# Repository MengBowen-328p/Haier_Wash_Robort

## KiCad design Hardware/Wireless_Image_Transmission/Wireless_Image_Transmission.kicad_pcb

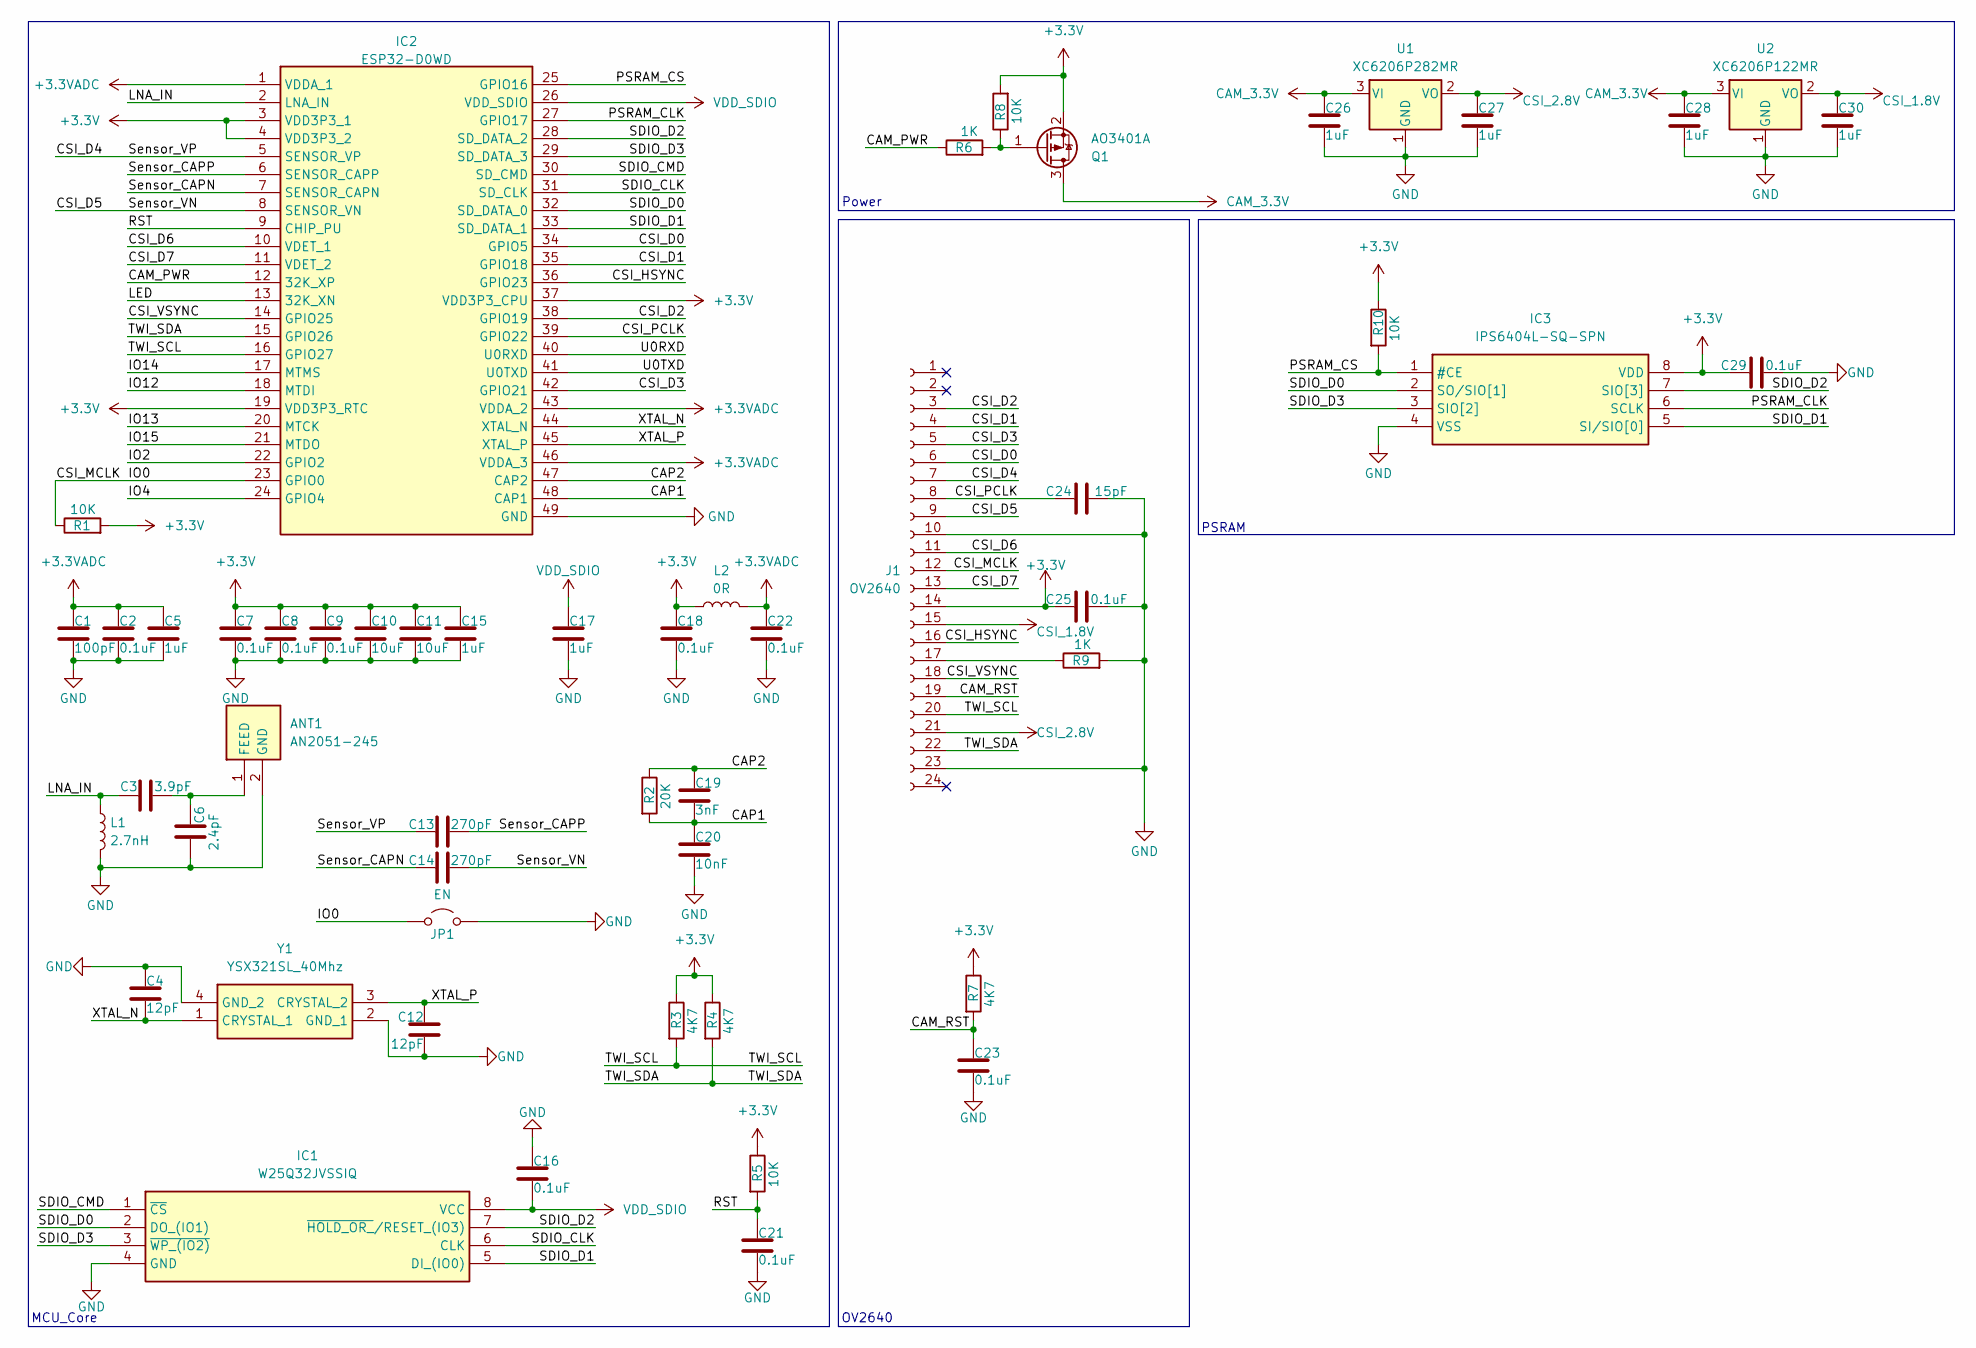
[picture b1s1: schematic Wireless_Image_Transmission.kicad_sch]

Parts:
ANT1: AN2051-245; ANTC5020X127N; Manufacturer_Part_Number AN2051-245
C1: 100pF; C_0402_1005Metric
C2, C7, C8, C9, C16, C18, C21, C22, C23, C25, C29: 0.1uF; C_0402_1005Metric
C3: 3.9pF; C_0402_1005Metric
C4, C12: 12pF; C_0402_1005Metric
C5, C15, C17: 1uF; C_0402_1005Metric
C6: 2.4pF; C_0402_1005Metric
C10, C11: 10uF; C_0402_1005Metric
C13, C14: 270pF; C_0402_1005Metric
C19: 3nF; C_0402_1005Metric
C20: 10nF; C_0402_1005Metric
C24: 15pF; C_0402_1005Metric
C26, C27, C28, C30: 1uF; C_0603_1608Metric
IC1: W25Q32JVSSIQ; SOIC127P790X216-8N; Manufacturer_Part_Number W25Q32JVSSIQ; Mouser Part Number 454-W25Q32JVSSIQ
IC2: ESP32-D0WD; QFN40P600X600X90-49N-D; Manufacturer_Part_Number ESP32-D0WD; Mouser Part Number 356-ESP32-D0WD
IC3: IPS6404L-SQ-SPN; SOIC127P600X175-8N; Manufacturer_Part_Number IPS6404L-SQ-SPN
J1: OV2640; TE_2-1734839-4_1x24-1MP_P0.5mm_Horizontal
JP1: EN; SolderJumper-2_P1.3mm_Open_RoundedPad1.0x1.5mm
L1: 2.7nH; L_0402_1005Metric_Pad0.77x0.64mm_HandSolder
L2: 0R; L_0402_1005Metric_Pad0.77x0.64mm_HandSolder
Q1: AO3401A; SOT-23
R1, R5, R8, R10: 10K; R_0402_1005Metric
R2: 20K; R_0402_1005Metric
R3, R4, R7: 4K7; R_0402_1005Metric
R6, R9: 1K; R_0402_1005Metric
U1: XC6206P282MR; SOT-23-3
U2: XC6206P122MR; SOT-23-3
Y1: YSX321SL_40Mhz; YSX321SL; Manufacturer_Part_Number YSX321SL

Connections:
+3.3V: C7.1, C8.1, C9.1, C10.1, C11.1, C15.1, C18.1, C25.1, C29.1, IC2.3 (VDD3P3_1), IC2.4 (VDD3P3_2), IC2.19 (VDD3P3_RTC), IC2.37 (VDD3P3_CPU), IC3.8 (VDD), J1.14, L2.1, Q1.2 (S), R1.2, R3.1, R4.1, R5.1, R7.1, R8.2, R10.1
+3.3VADC: C1.1, C2.1, C5.1, C22.1, IC2.1 (VDDA_1), IC2.43 (VDDA_2), IC2.46 (VDDA_3), L2.2
/CAM_PWR: IC2.12 (32K_XP), R6.1
/CAM_RST: C23.1, J1.19, R7.2
/CAP1: C19.2, C20.1, IC2.48 (CAP1), R2.2
/CAP2: C19.1, IC2.47 (CAP2), R2.1
/CSI_D0: IC2.34 (GPIO5), J1.6
/CSI_D1: IC2.35 (GPIO18), J1.4
/CSI_D2: IC2.38 (GPIO19), J1.3
/CSI_D3: IC2.42 (GPIO21), J1.5
/CSI_D4: C13.1, IC2.5 (SENSOR_VP), J1.7
/CSI_D5: C14.2, IC2.8 (SENSOR_VN), J1.9
/CSI_D6: IC2.10 (VDET_1), J1.11
/CSI_D7: IC2.11 (VDET_2), J1.13
/CSI_HSYNC: IC2.36 (GPIO23), J1.16
/CSI_MCLK: IC2.23 (GPIO0), J1.12, JP1.1 (A), R1.1
/CSI_PCLK: C24.1, IC2.39 (GPIO22), J1.8
/CSI_VSYNC: IC2.14 (GPIO25), J1.18
/IO2: IC2.22 (GPIO2)
/IO4: IC2.24 (GPIO4)
/IO12: IC2.18 (MTDI)
/IO13: IC2.20 (MTCK)
/IO14: IC2.17 (MTMS)
/IO15: IC2.21 (MTDO)
/LED: IC2.13 (32K_XN)
/LNA_IN: C3.1, IC2.2 (LNA_IN), L1.1
/PSRAM_CLK: IC2.27 (GPIO17), IC3.6 (SCLK)
/PSRAM_CS: IC2.25 (GPIO16), IC3.1 (#CE), R10.2
/RST: C21.1, IC2.9 (CHIP_PU), R5.2
/SDIO_CLK: IC1.6 (CLK), IC2.31 (SD_CLK)
/SDIO_CMD: IC1.1 (~CS), IC2.30 (SD_CMD)
/SDIO_D0: IC1.2 (DO_(IO1)), IC2.32 (SD_DATA_0), IC3.2 (SO/SIO[1])
/SDIO_D1: IC1.5 (DI_(IO0)), IC2.33 (SD_DATA_1), IC3.5 (SI/SIO[0])
/SDIO_D2: IC1.7 (~HOLD_OR_/RESET_(IO3)), IC2.28 (SD_DATA_2), IC3.7 (SIO[3])
/SDIO_D3: IC1.3 (~WP_(IO2)), IC2.29 (SD_DATA_3), IC3.3 (SIO[2])
/Sensor_CAPN: C14.1, IC2.7 (SENSOR_CAPN)
/Sensor_CAPP: C13.2, IC2.6 (SENSOR_CAPP)
/TWI_SCL: IC2.16 (GPIO27), J1.20, R3.2
/TWI_SDA: IC2.15 (GPIO26), J1.22, R4.2
/U0RXD: IC2.40 (U0RXD)
/U0TXD: IC2.41 (U0TXD)
/XTAL_N: C4.2, IC2.44 (XTAL_N), Y1.1 (CRYSTAL_1)
/XTAL_P: C12.1, IC2.45 (XTAL_P), Y1.3 (CRYSTAL_2)
CAM_3.3V: C26.1, C28.1, Q1.3 (D), U1.3 (VI), U2.3 (VI)
CSI_1.8V: C30.1, J1.15, U2.2 (VO)
CSI_2.8V: C27.1, J1.21, U1.2 (VO)
GND: ANT1.2 (GND), C1.2, C2.2, C4.1, C5.2, C6.2, C7.2, C8.2, C9.2, C10.2, C11.2, C12.2, C15.2, C16.1, C17.2, C18.2, C20.2, C21.2, C22.2, C23.2, C24.2, C25.2, C26.2, C27.2, C28.2, C29.2, C30.2, IC1.4 (GND), IC2.49 (GND), IC3.4 (VSS), J1.10, J1.23, JP1.2 (B), L1.2, R9.2, U1.1 (GND), U2.1 (GND), Y1.2 (GND_1), Y1.4 (GND_2)
unnamed: ANT1.1 (FEED), C3.2, C6.1
unnamed: J1.17, R9.1
unnamed: Q1.1 (G), R6.2, R8.1
VDD_SDIO: C16.2, C17.1, IC1.8 (VCC), IC2.26 (VDD_SDIO)

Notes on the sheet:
Power
PSRAM
OV2640
MCU_Core

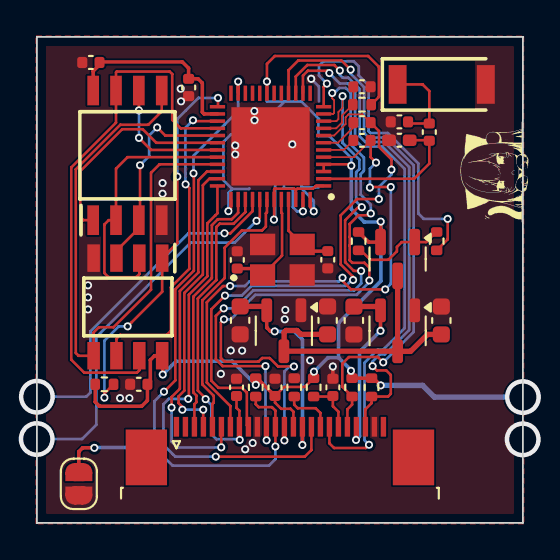
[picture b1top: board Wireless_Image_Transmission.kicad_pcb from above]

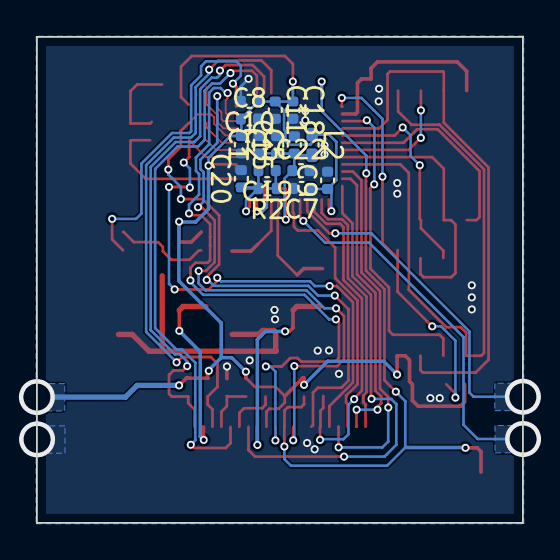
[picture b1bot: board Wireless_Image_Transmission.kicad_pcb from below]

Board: 2 copper layers, 27.0 x 27.0 mm, 52 parts (15 on the bottom side), 42 nets.

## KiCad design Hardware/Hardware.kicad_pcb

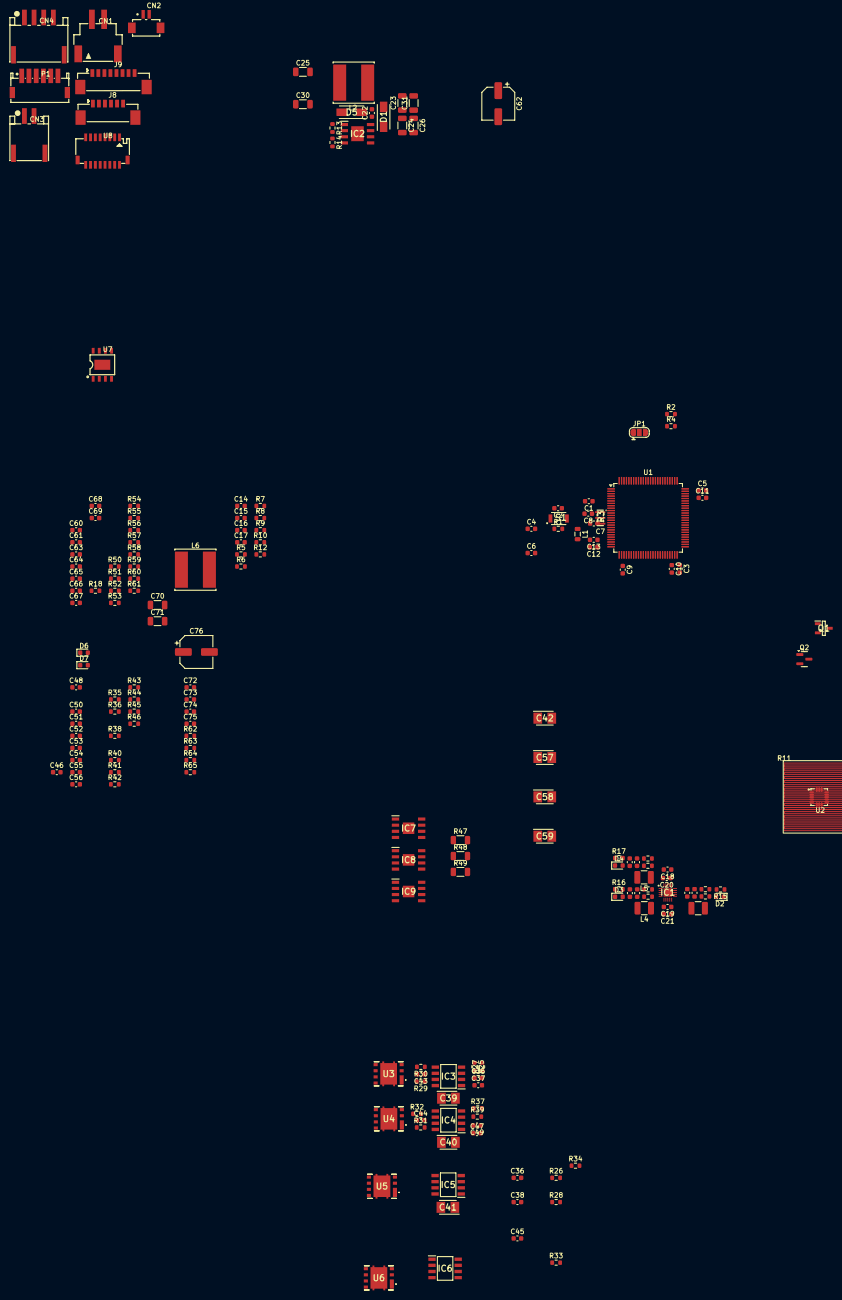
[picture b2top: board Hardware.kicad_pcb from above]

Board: 2 copper layers, 182 parts (0 on the bottom side), 103 nets, no tracks yet.

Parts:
C1, C2, C3, C4, C5, C6, C7, C8, C9, C12, C14, C16, C22, C35, C36, C37, C38, C47, C48, C49, C50, C51, C52, C53, C54, C55, C56, C61, C63, C66, C72, C73, C74, C75: 0.1uF; C_0603_1608Metric
C10, C11: 2.2uF; C_0603_1608Metric
C13, C15, C43, C44, C45, C46, C64, C65, C68, C69: 1uF; C_0603_1608Metric
C17: 0.01uF; C_0603_1608Metric
C18, C19, C20, C21, C32, C33, C34: 10uF; C_0603_1608Metric
C23, C24, C25: 1uF; C_1206_3216Metric
C26, C30, C31, C70, C71: 10uF; C_1206_3216Metric
C27, C28, C29: 220pF; C_0603_1608Metric
C39, C40, C41, C42, C57, C58, C59: 100uF; CAPPM3528X210N
C60: 22uF; C_0603_1608Metric
C62, C76: 100uF; CP_Elec_6.3x7.7
C67: 100pF; C_0603_1608Metric
CN1: 2.54-2P_WT; CONN-SMD_2.54-2PWT
CN2: DF13B-2P-1.25V(51); CONN-TH_2P-P1.25_HRS_DF13B-2P-1.25V-51
CN3: UK-2.0-2AWT; CONN-SMD_2P-P2.00_USAKRO_UK-2.0-2AWT
CN4: UK-2.0-4AWT; CONN-SMD_4P-P2.00_USAKRO_UK-2.0-4AWT
D1, D5: SS54; DIOM5126X245N
D2: 3.3V_MCU; LED_0603_1608Metric
D3: 3.3V_Sensor; LED_0603_1608Metric
D4: 3.3V_WirelessModule; LED_0603_1608Metric
D6: 5V; LED_0603_1608Metric
D7: Charge; LED_0603_1608Metric
IC1: EA3036QBR; QFN40P300X300X80-21N
IC2: TPS5450DDAR; SOIC127P600X170-9N
IC3, IC4, IC5, IC6: IR2104SPBF; SOIC127P600X175-8N
IC7, IC8, IC9: TB67H450FNG; SOIC127P600X175-9N
J8: SMD1.25-6P; SMD-1.25-6P
J9: SMD1.25-8P; SMD-1.25-8P
JP1: BOOT0; SolderJumper-3_P1.3mm_Open_RoundedPad1.0x1.5mm
L1: 0R; L_0805_2012Metric
L2: 15uH; L_Cenker_CKCS8060
L3, L4, L5: 1.5uH; L_1210_3225Metric
L6: 10uH; L_Cenker_CKCS8060
P1: Header_6; CONN-SMD-6P-1.5
Q1: AO3400; SOT95P280X125-3N
Q2: AO3401A; SOT-23
R1, R9, R13, R15, R16, R17, R18, R50, R56: 10K; R_0603_1608Metric
R2, R4, R8: 100R; R_0603_1608Metric
R3: CSTCE16M00G55-R0; CSTCE12M0G55-R0
R5, R6, R7, R29, R30, R31, R32, R33, R34, R35, R36: 22R; R_0603_1608Metric
R10, R12: 500R; R_0603_1608Metric
R11: IMU_Heater
R14: 3.16K; R_0603_1608Metric
R19, R21, R23: 68K; R_0603_1608Metric
R20, R22, R24: 15K; R_0603_1608Metric
R25, R26, R27, R28, R37, R38, R39, R40, R41, R42, R43, R44, R45, R46, R52, R62, R63, R64, R65: 1K; R_0603_1608Metric
R47, R48, R49: 100mR; R_1206_3216Metric
R51: 2.6K; R_0603_1608Metric
R53, R59: 100K; R_0603_1608Metric
R54, R57: 5R1; R_0603_1608Metric
R55, R61: 82K; R_0603_1608Metric
R58: 510K; R_0603_1608Metric
R60: 51K; R_0603_1608Metric
S1: RST; B3U-1000P
U1: STM32F407VETx; LQFP-100_14x14mm_P0.5mm
U2: ICM20602
U3, U4, U5, U6: CSD87350Q5D
U7: IP2364; ESOP-8_L4.9-W3.9-P1.27-LS6.0-BL-EP-3
U8: A1001WR-S-2X08PD01; CONN-SMD_A1001WR-S-2X08PD01

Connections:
+3.3V: C1.1, C3.1, C4.1, C5.1, C7.1, C8.1, C9.1, C17.2, L1.1, R1.1, R2.2, U1.6 (VBAT), U1.11 (VDD), U1.19 (VDD), U1.28 (VDD), U1.50 (VDD), U1.75 (VDD), U1.100 (VDD), U2.1 (VDDIO), U2.16 (VDD)
+3.3VADC: C6.1, C12.1, C13.1, L1.2, U1.21 (VREF+), U1.22 (VDDA)
+3.3V_MCU: C27.1, C32.1, D2.2 (A), L3.2, R19.1
+3.3V_Sensor: C28.1, C33.1, D3.2 (A), L4.2, R21.1
+3.3V_WirelessModule: C29.1, C34.1, D4.2 (A), L5.2, R23.1
+5V: C18.1, C19.1, C20.1, C21.1, C25.1, C30.1, C62.1, D6.2 (A), IC1.7 (VIN2), IC1.8 (EN2), IC1.9 (EN1), IC1.10 (VIN1), IC1.16 (VCC), IC1.18 (EN3), IC1.19 (VIN3), L2.2, R13.1
/Brush_Motor/L_Wheel+: U3.6 (VSW_1), U3.7 (VSW_2), U3.8 (VSW_3)
/Brush_Motor/L_Wheel-: U4.6 (VSW_1), U4.7 (VSW_2), U4.8 (VSW_3)
/Brush_Motor/L_Wheel_Motor_IN1: C37.2, IC3.2 (IN), R27.2
/Brush_Motor/L_Wheel_Motor_IN2: C49.2, IC4.2 (IN), R39.2
/Brush_Motor/L_Wheel_Motor_SD1: IC3.3 (~SD), IC4.3 (~SD)
/Brush_Motor/R_Wheel+: U5.6 (VSW_1), U5.7 (VSW_2), U5.8 (VSW_3)
/Brush_Motor/R_Wheel-: U6.6 (VSW_1), U6.7 (VSW_2), U6.8 (VSW_3)
/Brush_Motor/R_Wheel_Motor_IN1: C38.2, IC5.2 (IN), R28.2
/Brush_Motor/R_Wheel_Motor_IN2: C50.2, IC6.2 (IN), R40.2
/Brush_Motor/R_Wheel_Motor_SD1: IC5.3 (~SD), IC6.3 (~SD)
/Brushless_Motor/Turbo_FB_OUT: C75.2, R65.2
/Brushless_Motor/Turbo_PWM_OUT: C73.2, R63.2
/MCU_Core/BOOT0: JP1.2 (C), U1.94 (BOOT0)
/MCU_Core/NRST: C2.1, R1.2, S1.2 (A), U1.14 (NRST)
/MCU_Core/OSCH_IN: R3.1, U1.12 (PH0)
/MCU_Core/OSCH_OUT: R3.3, U1.13 (PH1)
/MCU_Core/VCAP_1: C10.1, U1.49 (VCAP_1)
/MCU_Core/VCAP_2: C11.1, U1.73 (VCAP_2)
/Power_Supply/V_BAT: R50.1, R51.2
/Power_Supply/V_BAT_EN: R52.2, R53.2
/Sensors/IMU_CLK: R5.1, R5.2, U2.2 (SCL)
/Sensors/IMU_MISO: R7.1, R7.2, U2.4 (AD0)
/Sensors/IMU_MOSI: R6.1, R6.2, U2.3 (SDA)
/Sensors/REGOUT: C16.1, U2.14 (REGOUT)
/Sensors/VDD: C14.2, C15.2
BAT_Charge: C67.2, C68.1, C69.1, C70.1, C71.1, L6.2, R58.1
GND: C1.2, C2.2, C3.2, C4.2, C5.2, C6.2, C7.2, C8.2, C9.2, C10.2, C11.2, C12.2, C13.2, C14.1, C15.1, C16.2, C17.1, C18.2, C19.2, C20.2, C21.2, C23.2, C24.2, C25.2, C26.2, C30.2, C31.2, C32.2, C33.2, C34.2, C35.1, C36.1, C37.1, C38.1, C39.2, C40.2, C41.2, C42.2, C47.1, C48.1, C49.1, C50.1, C51.1, C52.1, C53.1, C54.1, C54.2, C55.1, C55.2, C56.1, C56.2, C57.2, C58.2, C59.2, C60.1, C61.1, C62.2, C63.1, C64.1, C65.1, C68.2, C69.2, C70.2, C71.2, C72.1, C73.1, C74.1, C75.1, C76.2, D5.2 (A), D7.1 (K), IC1.1 (GND3), IC1.4 (GND2_1), IC1.5 (GND2_2), IC1.12 (GND1_1), IC1.13 (GND1_2), IC1.15 (AGND_1), IC1.17 (AGND_2), IC1.21 (EP), IC2.6 (GND), IC2.9 (EP), IC3.4 (COM), IC4.4 (COM), IC5.4 (COM), IC6.4 (COM), IC7.1 (GND), IC7.4 (VREF), IC7.9 (EP), IC8.1 (GND), IC8.4 (VREF), IC8.9 (EP), IC9.1 (GND), IC9.4 (VREF), IC9.9 (EP), Q1.2 (S), R3.2, R4.2, R9.1, R14.2, R15.2, R16.2, R17.2, R18.2, R20.2, R22.2, R24.2, R25.1, R26.1, R37.1, R38.1, R41.1, R42.1, R43.1, R44.2, R45.2, R46.2, R47.2, R48.2, R49.2, R51.1, R56.2, R59.2, R60.1, R62.1, R64.1, S1.1 (K), U1.10 (VSS), U1.20 (VSSA), U1.27 (VSS), U1.74 (VSS), U1.99 (VSS), U2.9 (RESV), U2.10 (RESV), U2.11 (RESV), U2.12 (RESV), U2.13 (GND), U2.15 (RESV), U3.9 (PGND_1), U3.10 (PGND_2), U3.11 (PGND_3), U3.12 (PGND_4), U3.13 (PGND_5), U4.9 (PGND_1), U4.10 (PGND_2), U4.11 (PGND_3), U4.12 (PGND_4), U4.13 (PGND_5), U5.9 (PGND_1), U5.10 (PGND_2), U5.11 (PGND_3), U5.12 (PGND_4), U5.13 (PGND_5), U6.9 (PGND_1), U6.10 (PGND_2), U6.11 (PGND_3), U6.12 (PGND_4), U6.13 (PGND_5), U7.9 (GND)
unnamed: C35.2, R25.2, R27.1
unnamed: C36.2, R26.2, R28.1
unnamed: C47.2, R37.2, R39.1
unnamed: C48.2, R38.2, R40.1
unnamed: C51.2, R41.2, R44.1
unnamed: C52.2, R42.2, R45.1
unnamed: C53.2, R43.2, R46.1
unnamed: C64.2, R54.2
unnamed: C65.2, R57.2
unnamed: C72.2, R62.2, R63.1
unnamed: C74.2, R64.2, R65.1
unnamed: D1.1 (K), IC2.7 (VIN)
unnamed: D2.1 (K), R15.1
unnamed: D3.1 (K), R16.1
unnamed: D4.1 (K), R17.1
unnamed: C22.2, D5.1 (K), IC2.8 (PH), L2.1
unnamed: D6.1 (K), R18.1
unnamed: D7.2 (A), R61.2
unnamed: C27.2, IC1.14 (FB1), R19.2, R20.1
unnamed: IC1.11 (LX1), L3.1
unnamed: C28.2, IC1.3 (FB2), R21.2, R22.1
unnamed: IC1.6 (LX2), L4.1
unnamed: C29.2, IC1.2 (FB3), R23.2, R24.1
unnamed: IC1.20 (LX3), L5.1
unnamed: C22.1, IC2.1 (BOOT)
unnamed: IC2.4 (VSENSE), R13.2, R14.1
unnamed: IC3.7 (HO), R29.1
unnamed: IC3.5 (LO), R30.1
unnamed: C43.1, IC3.8 (VB)
unnamed: C43.2, IC3.6 (VS), U3.4 (TGR)
unnamed: IC4.7 (HO), R31.1
unnamed: IC4.5 (LO), R32.1
unnamed: C44.1, IC4.8 (VB)
unnamed: C44.2, IC4.6 (VS), U4.4 (TGR)
unnamed: IC5.7 (HO), R33.1
unnamed: IC5.5 (LO), R34.1
unnamed: C45.1, IC5.8 (VB)
unnamed: C45.2, IC5.6 (VS), U5.4 (TGR)
unnamed: IC6.7 (HO), R35.1
unnamed: IC6.5 (LO), R36.1
unnamed: C46.1, IC6.8 (VB)
unnamed: C46.2, IC6.6 (VS), U6.4 (TGR)
unnamed: IC7.7 (RS), R47.1
unnamed: IC8.7 (RS), R48.1
unnamed: IC9.7 (RS), R49.1
unnamed: JP1.1 (A), R2.1
unnamed: JP1.3 (B), R4.1
unnamed: Q1.3 (D), R12.2
unnamed: Q1.1 (G), R8.2, R9.2
unnamed: Q2.3 (D), R50.2
unnamed: Q2.1 (G), R52.1
unnamed: R10.2, R11.1
unnamed: R11.2, R12.1
unnamed: R30.2, U3.5 (BG)
unnamed: R29.2, U3.3 (TG)
unnamed: R32.2, U4.5 (BG)
unnamed: R31.2, U4.3 (TG)
unnamed: R34.2, U5.5 (BG)
unnamed: R33.2, U5.3 (TG)
unnamed: R36.2, U6.5 (BG)
unnamed: R35.2, U6.3 (TG)
unnamed: C66.1, U7.7 (BST)
unnamed: C67.1, R58.2, R59.1, U7.6 (FB)
unnamed: R61.1, U7.4 (LED)
unnamed: C66.2, L6.1, R57.1, U7.8 (LX)
unnamed: R60.2, U7.5 (NTC)
unnamed: R55.2, R56.1, U7.3 (VINSEN)
unnamed: C60.2, C61.2, U7.1 (VSYS)
VCC: C23.1, C24.1, C26.1, C31.1, C39.1, C40.1, C41.1, C42.1, C57.1, C58.1, C59.1, D1.2 (A), IC3.1 (VCC), IC4.1 (VCC), IC5.1 (VCC), IC6.1 (VCC), IC7.5 (VM), IC8.5 (VM), IC9.5 (VM), Q2.2 (S), R10.1, R53.1, U3.1 (VIN), U4.1 (VIN), U5.1 (VIN), U6.1 (VIN)
VCC_Charge: C63.2, C76.1, R54.1, R55.1, U7.2 (VIN)

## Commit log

2024-09-30 Init SCH
2024-10-01 Finished SCH MCU
2024-10-02 Finished IMU SCH
2024-10-04 Add Image Transmission
2024-10-05 Init PCB
2024-10-27 Update SCH
2024-10-27 Update PCB
